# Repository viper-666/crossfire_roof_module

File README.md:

# XF Roof Module

Deutsche Anleitung: [LIESMICH.md](https://github.com/viper-666/crossfire_roof_module/blob/master/LIESMICH.md)

This module allows you to open / close the Crossfire's convertible top without having to press and hold the Open / Close button all the time.

Another feature is that you can set up the speed at which you can do this in the Arduino Sketch.
The default is 31 mph (50 kph) (variable "int GESCHWINDIGKEIT = 50" attention it is in kph not in mph) and should not be increased. If the speed at which you open the convertible top is too high, this will damage your convertible top or the mechanics.

In addition, the windows are automatically raised after the convertible top is opened.
There is also an emergency stop function simply push the button, no matter which direction, again and the convertible top stops.

I have tested the module for several months without problems but it could damage your car. Therefore, a replica is done at your own risk!

## Handling

If you want to open or close the roof while the car stands simply press the switch short in the appropriate direction. It can take up to 2 seconds before the roof moves. If an error occurs it will piping.
During the journey, you can open or close the convertible top up to the set speed. 

Please note the following:

If you want to open the convertible top while driving, it is very important first to press the switch open and then to unlock the convertible top within 2 seconds.
If you unlock the convertible top first, the original CrossFire convertible module is interrupted and you have to close the convertible top again and wait a few seconds until you can open it.

When closing while driving up to the set speed, there is nothing else to do, just press the switch on close and after about 2 seconds the convertible top will close.
If you get over the set speed while opening or closing, the convertible top stops moving and you have to speed down under the set speed and the convertible top will complete the action.

## Lets start

First you have to build the hardware, so solder the board. 

## BOM Hardware

|Microcontroler:| |
|---|---|
|Value		|Quantily|
|Arduino Nano V3|1     |

|Resistors:| |
|---|---|
|Value|Quantily|
|1M |1 |
|2k2 |3 |
|5k |2 |
|22k |5 |
|100k |5 |
|560k |1 |
|200 |1 |

|Zener Diode:| |
|---|---|
|Value|Quantily|
|1N750 (4,7V)|1|

|Diode:| |
|---|---|
|Value|Quantily|
|1N4007|1|

|Voltage regulator:| |
|---|---|
|Value|Quantily|
|78L05Z (5V) TO92|1|

|Capacitors:| |
|---|---|
|Value|Quantily|
|100µF|2|
|100n|2|

|Transistors:| |
|---|---|
|Value|Quantily|
|BC547|5|

|Fuse:| |
|---|---|
|Value|Quantily|
|200mA|1|
|Fuse holder|1|

|Plug and socket:| |
|---|---|
|Value|Quantily|
|TE Connectivity AMP 1-1586041-4 VAL-U-LOK CONN HEADER 14POS R/A W/O PEGS|1 or 2|
|TE Connectivity AMP 1-1586019-4 VAL-U-LOK CONN RCPT HOUSING 14POS 4.2MM|1 or 2|
|TE Connectivity AMP 1586315-1 CONN TERM SOCKET 18-22AWG TIN|14 or 28|

But you can take any other socket and plug as long as they have at least 8 contacts.

## Building the hardware

A PCB measuring 90mm x 53mm is required for assembly.

First I soldered the small parts than the Arduino and the socket. 

Subsequently, I have constructed the board according to the [schematic](https://github.com/viper-666/xf_roof_module/blob/master/Dachmodul.pdf):

The plug with the cables is created according to the following [schema](https://github.com/viper-666/xf_roof_module/blob/master/Wiring.pdf) and integrated into the Crossfire cable harness.
The PINs marked in blue belong to the corresponding PINs of the connector.
The pins for the plug should be crimped onto the stripped cable ends with a crimping tool. If you do not have a crimping pliers, it is cheap, you can get it for 10-20 $ or you can solder the cable ends with the pins.

This is how the finished module with the printed housing looks like:

I recommend the construction of a deactivation plug, which is inserted in case of problems or sale of the car instead of the roof module. Thus, the severed lines are reconnected and the "original state" is restored.
Simply connect the following pins for a socket:

|A|B|
|---|---|
|PIN 3|PIN 11|
|PIN 7|PIN 12|
|PIN 9|PIN 13|

## Installing of the firmware

Simply use the [Sketch](https://github.com/viper-666/crossfire_roof_module/blob/master/Crossfire_Dachmodul-4.ino) with the [ARDUINO IDE](https://www.arduino.cc/en/Main/Software) to the Arduino.

## Installation in the Crossfire

The plug created in the previous section with the cables is now wired according to the following [schema](https://github.com/viper-666/crossfire_roof_module/blob/master/Wiring.pdf) in the Crossfire.

I recommend soldering the cables and isolating them with a shrink tube.

We start at the roof switch. To get to the roof switch, open the cup holder, grasp the opening with the fingers and lift the silver bezel at the front of the circuit until it is released from the grid.

The white / purple cable must then be cut and the purple cable of our plug must be connected with the part of the white / purple cable which is still hanging on the plug. The black cable of the plug comes to the now still open end of the white / purple cable.
The white cable of our plug comes to the brown / yellow cable.

Now we have to lift the carpet in the passenger footwell and fold in the direction of the seat and remove the white styrophoric plate.

The silver plate is secured with 3 black plastic nuts, which must be removed.

Now we can fold this towards the seat. The wiring harness with the required cables is on the upper right.

In this harness we have to look for the following cables:
- Pink / Red / Black (+ 12V) which we connect with the red cable of the plug
- Brown (ground) this we will connect with the brown cables of the plug
- Blue / Green (BCM PIN 56) this must be cut through and the cable end which goes to the left to the center console comes the yellow and to the other end the blue cable of the plug
- Green / White (BCM PIN 74) you have to be careful, the cable is available several times. It is best to test with a multimeter in the continuity test whether the correct cable from the control unit PIN 74 has caught. Then this must cut through and to the cable end which goes to the left to the center console comes the orange and to the other end the green cable of the plug

If there is still enough space in the box for the RCM module and the control unit, the cables can also be tapped directly at the connector of the control unit and you only have to pass the three cables for the roof switch through the cable harness.
Advantage is, the better accessibility and one the cables unambiguously at the connector finds, since there the PIN numbers are readable.

## Built With

* [ARDUINO](https://www.arduino.cc/en/Main/Software) - I used the Version 1.6.8
* [EAGLE](https://www.autodesk.com/products/eagle/free-download) - The Software is free for peronal use but you have to make an Autodesk Account.

## Author

* **Andre Holtkamp** - [viper-666](https://github.com/viper-666)

## License

This project is licensed under the GNU General Public License v3.0 License - see the [LICENSE](https://github.com/viper-666/crossfire_roof_module/blob/master/LICENSE) file for details.

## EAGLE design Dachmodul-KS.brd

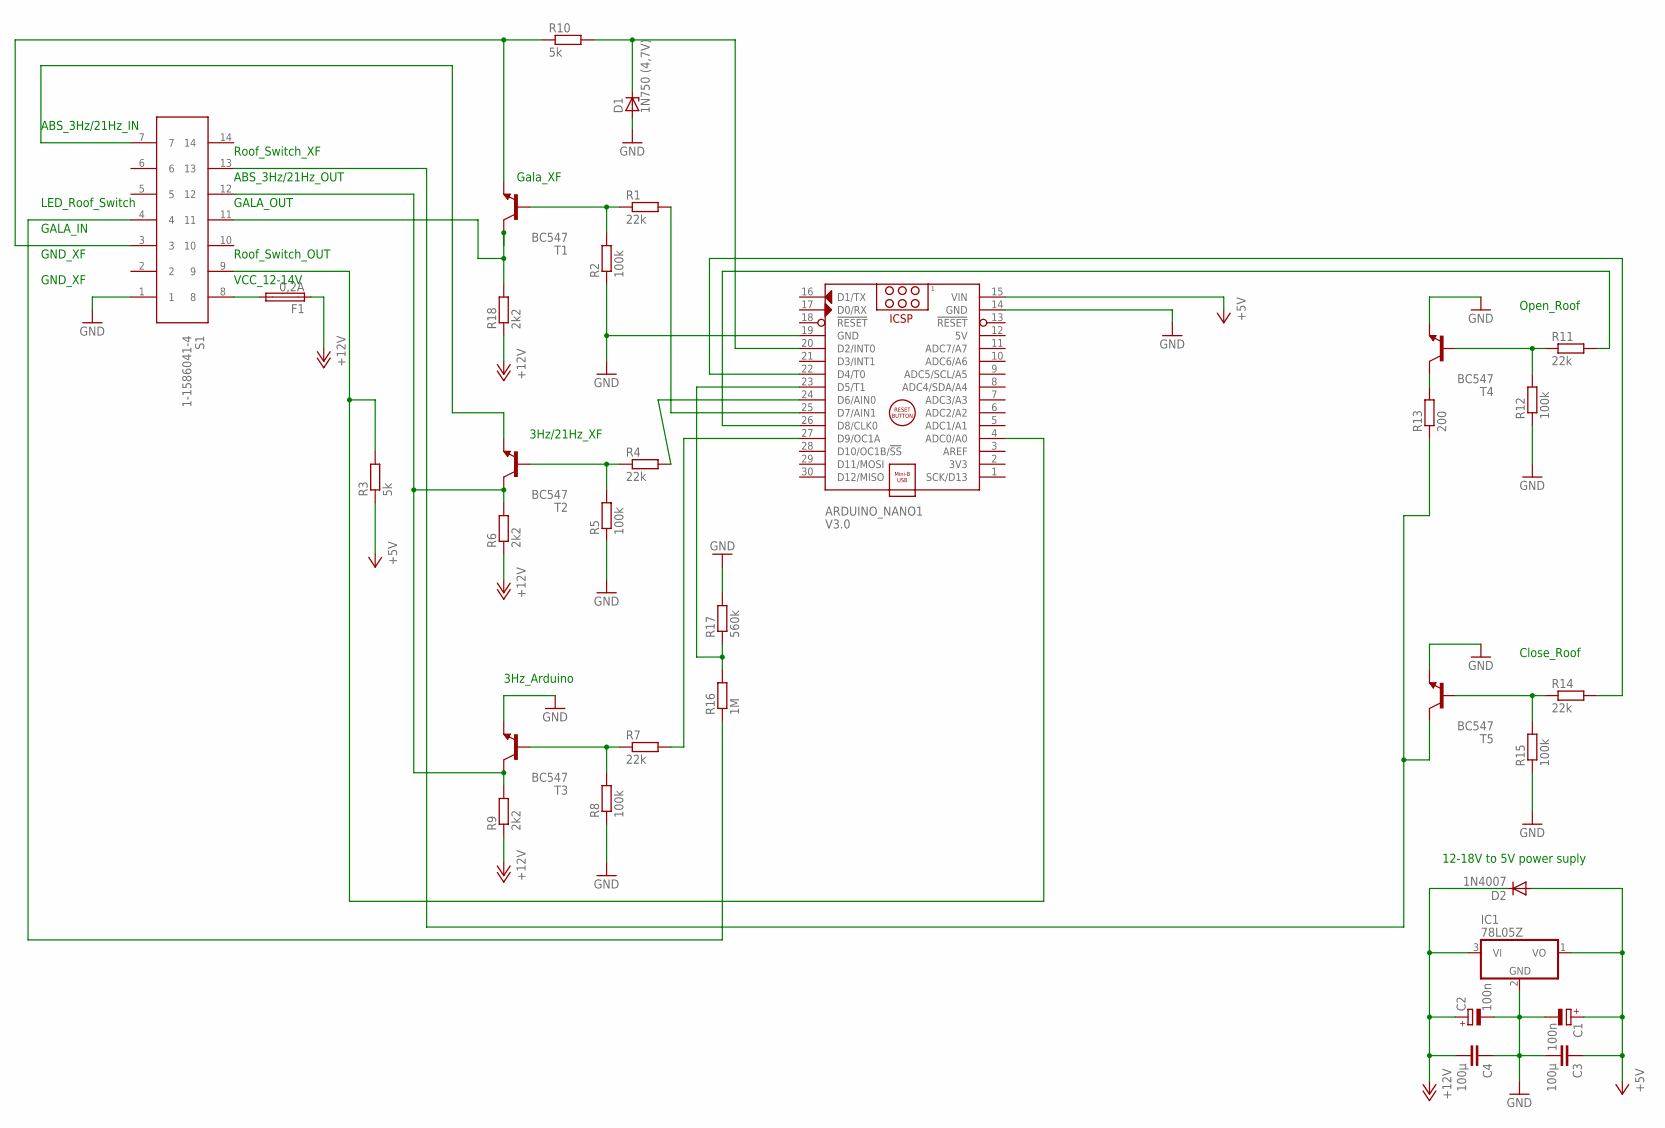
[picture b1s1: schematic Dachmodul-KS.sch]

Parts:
ARDUINO_NANO1: V3.0; ARDUINO_NANO
C1, C2: 100n; E3,5-8
C3, C4: 100µ; C025-025X050
D1: 1N750 (4,7V); ZDIO-2.5
D2: 1N4007; DO41-10
F1: 0,2A; SH22,5A
IC1: 78L05Z; TO92
R1, R4, R7, R11, R14: 22k; 0207/10
R2, R5, R8, R12, R15: 100k; 0207/10
R3, R10: 5k; 0207/10
R6, R9, R18: 2k2; 0207/10
R13: 200; 0207/10
R16: 1M; 0207/10
R17: 560k; 0207/10
S1: 1-1586041-4; 64901421022
T1, T2, T3, T4, T5: BC547; TO92

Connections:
5V: ARDUINO_NANO1.12 (5V)
+5V: ARDUINO_NANO1.15 (VIN), C1.+, C3.1, D2.A, IC1.1 (VO), R3.1
+12V: C2.+, C4.2, D2.C, F1.1, IC1.3 (VI), R6.1, R9.1, R18.1
GND: ARDUINO_NANO1.14 (GND), ARDUINO_NANO1.19 (GND), C1.-, C2.-, C3.2, C4.1, D1.A, IC1.2 (GND), R2.1, R5.1, R8.1, R12.1, R15.1, R17.2, S1.1, T3.1 (E), T4.1 (E), T5.1 (E)
unnamed: R1.1, R2.2, T1.2 (B)
unnamed: R18.2, S1.11, T1.3 (C)
unnamed: R4.1, R5.2, T2.2 (B)
unnamed: R6.2, R9.2, S1.12, T2.3 (C), T3.3 (C)
unnamed: R7.1, R8.2, T3.2 (B)
unnamed: ARDUINO_NANO1.27 (D9/OC1A), R7.2
unnamed: S1.7, T2.1 (E)
unnamed: ARDUINO_NANO1.24 (D6/AIN0), R4.2
unnamed: R10.1, S1.3, T1.1 (E)
unnamed: ARDUINO_NANO1.25 (D7/AIN1), R1.2
unnamed: F1.2, S1.8
unnamed: R13.2, T4.3 (C)
unnamed: R11.1, R12.2, T4.2 (B)
unnamed: ARDUINO_NANO1.26 (D8/CLK0), R11.2
unnamed: R13.1, S1.13, T5.3 (C)
unnamed: R14.1, R15.2, T5.2 (B)
unnamed: ARDUINO_NANO1.22 (D4/T0), R14.2
unnamed: R16.1, S1.4
unnamed: ARDUINO_NANO1.23 (D5/T1), R16.2, R17.1
unnamed: ARDUINO_NANO1.4 (ADC0/A0), R3.2, S1.9
unnamed: ARDUINO_NANO1.20 (D2/INT0), D1.C, R10.2

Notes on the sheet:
ABS_3Hz/21Hz_OUT
ABS_3Hz/21Hz_IN
GALA_IN
GALA_OUT
VCC_12-14V
GND_XF
Roof_Switch_OUT
Roof_Switch_XF
LED_Roof_Switch
3Hz_Arduino
3Hz/21Hz_XF
Gala_XF
12-18V to 5V power suply
Open_Roof
Close_Roof

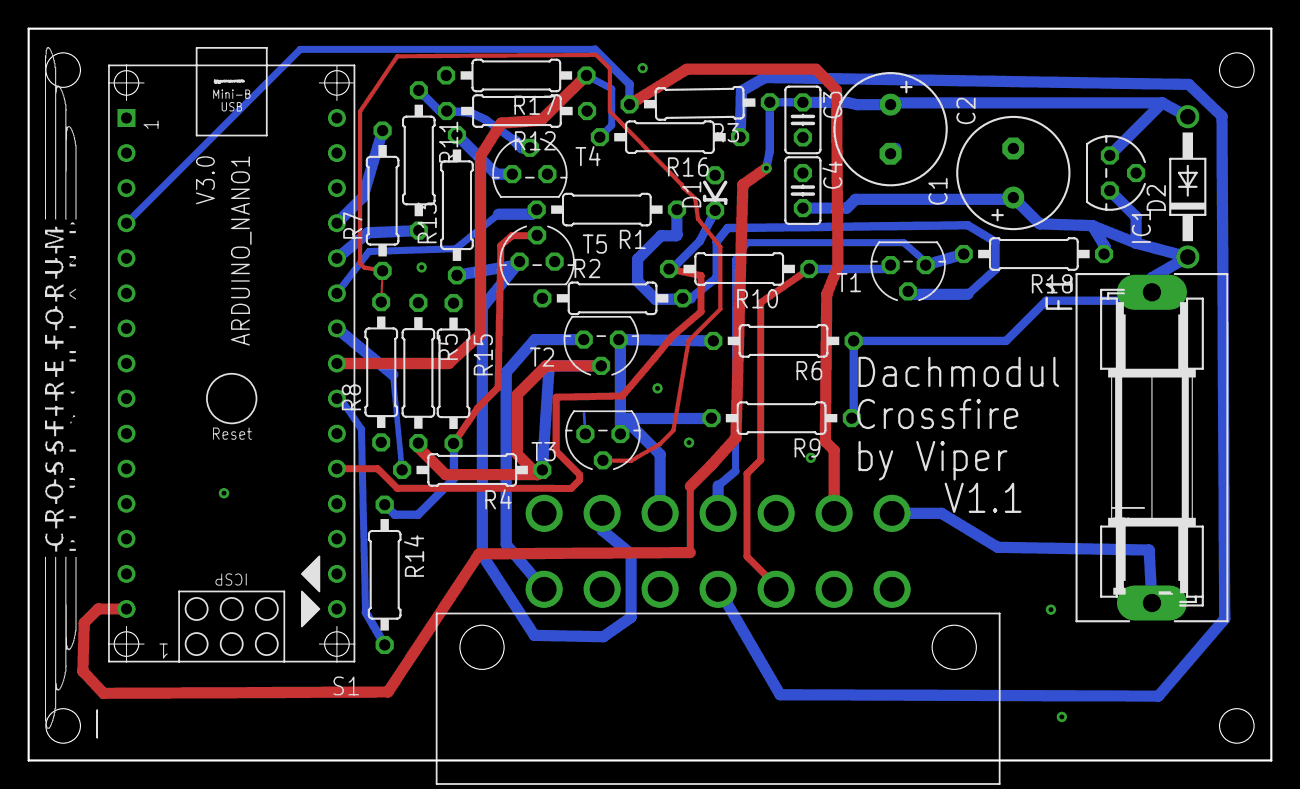
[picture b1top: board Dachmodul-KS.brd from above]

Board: 2 copper layers, 90.0 x 53.0 mm, 33 parts (0 on the bottom side), 24 nets.

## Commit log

2019-08-24 Create test
2019-08-29 Pictures with PCB
2019-08-29 Pictures new Linked
2019-08-29 Picture added
2019-08-29 Pictures updated
2019-12-29 Fehlerbehebung
    Es gab einen Fehler wenn das Dach während der Fahrt geöffnet wurde.

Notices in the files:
parts and their libraries:
Wuerth_Elektronik_eiCan_Mini_Power_Conne: Copyright: Würth Elektronik
